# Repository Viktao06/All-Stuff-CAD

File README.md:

Welcome! These are some of my works related to Computer Aided-Design (CAD). While they might not be the most beautiful or most efficient drawings, 
they helped me gain experience using computers to draw schematics, mechanical drawings and eventually, their 3D form.

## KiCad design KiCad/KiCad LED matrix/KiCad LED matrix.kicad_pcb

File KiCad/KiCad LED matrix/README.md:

This design was one of our candidates for printing and building our LED matrix animation project on. 
Although the design was a little bulky and wasn't chosen in the end, it was still fun to make and helped me familiarize myself with KiCAD.

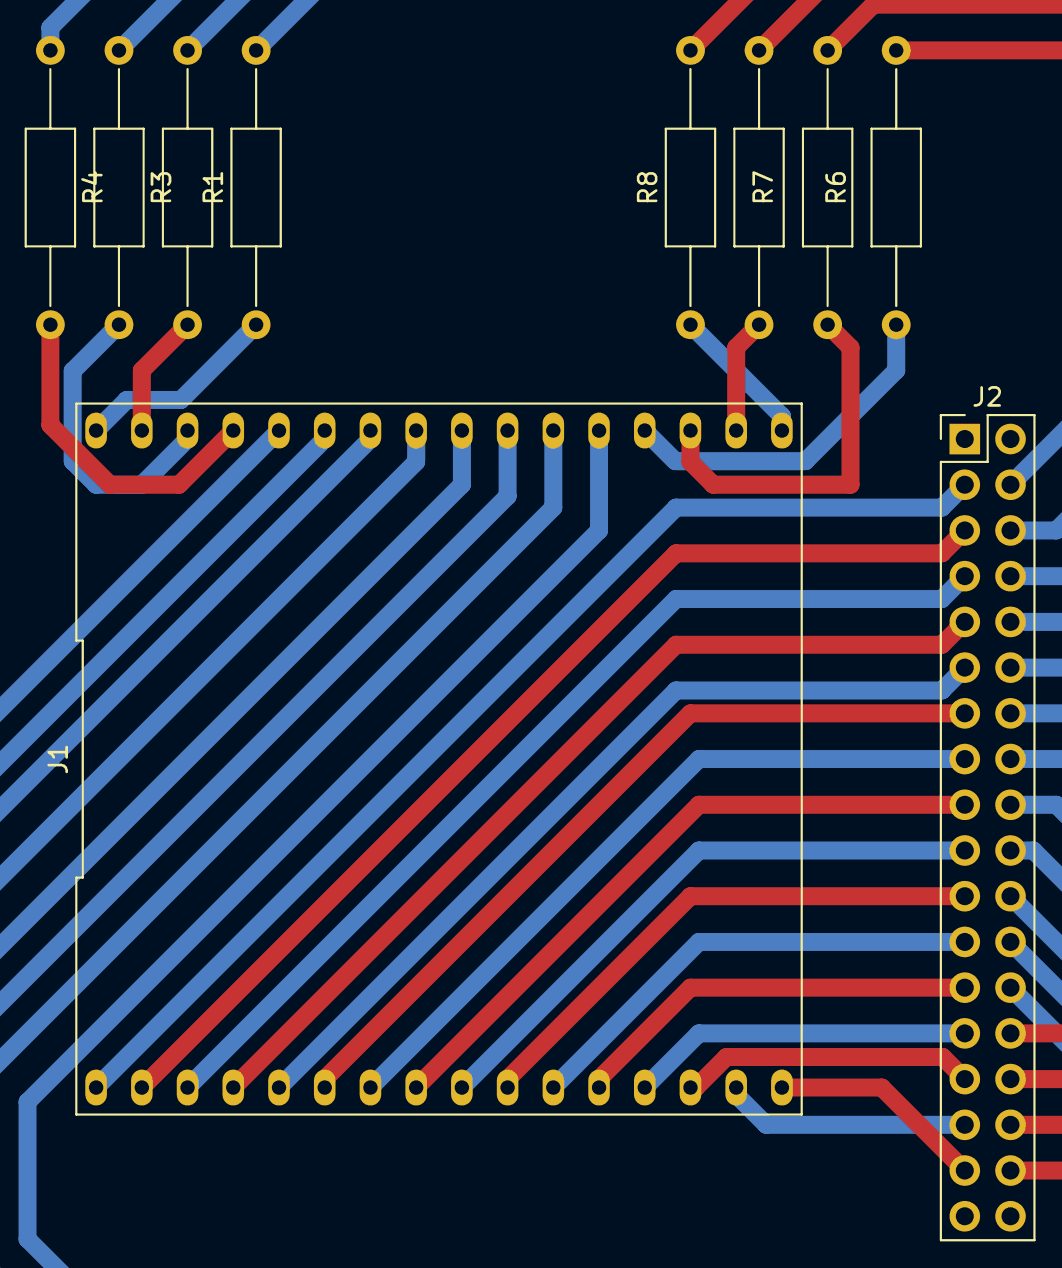
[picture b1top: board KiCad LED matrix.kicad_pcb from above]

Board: 2 copper layers, 10 parts (0 on the bottom side), 40 nets.

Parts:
J1: Matrix Connection; RGB Matrix 2.54 pitch
J2: Conn_02x18_Counter_Clockwise; PinHeader_2x18_P2.54mm_Vertical
R1, R2, R3, R4, R5, R6, R7, R8: 330; R_Axial_DIN0207_L6.3mm_D2.5mm_P15.24mm_Horizontal

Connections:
unnamed: J1.1, J2.1
unnamed: J1.2, J2.2
unnamed: J1.3, J2.3
unnamed: J1.4, J2.4
unnamed: J1.5, J2.5
unnamed: J1.6, J2.6
unnamed: J1.7, J2.7
unnamed: J1.8, J2.8
unnamed: J1.9, J2.9
unnamed: J1.10, J2.10
unnamed: J1.11, J2.11
unnamed: J1.12, J2.12
unnamed: J1.13, J2.13
unnamed: J1.14, J2.14
unnamed: J1.15, J2.15
unnamed: J1.16, J2.16
unnamed: J1.17, R1.1
unnamed: J1.18, R2.2
unnamed: J1.19, R3.2
unnamed: J1.20, R4.2
unnamed: J1.21, J2.21
unnamed: J1.22, J2.22
unnamed: J1.23, J2.23
unnamed: J1.24, J2.24
unnamed: J1.25, J2.25
unnamed: J1.26, J2.26
unnamed: J1.27, J2.27
unnamed: J1.28, J2.28
unnamed: J1.29, R5.1
unnamed: J1.30, R6.1
unnamed: J1.31, R7.1
unnamed: J1.32, R8.1
unnamed: J2.17, R1.2
unnamed: J2.18, R2.1
unnamed: J2.19, R3.1
unnamed: J2.20, R4.1
unnamed: J2.29, R5.2
unnamed: J2.30, R6.2
unnamed: J2.31, R7.2
unnamed: J2.32, R8.2

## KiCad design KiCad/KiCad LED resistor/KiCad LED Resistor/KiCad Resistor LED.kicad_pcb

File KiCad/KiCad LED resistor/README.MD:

My very first experience using KiCAD. We made a simple schematic and drawing of a battery connected to a resistor and an LED. The drawing seemed to come out fine.

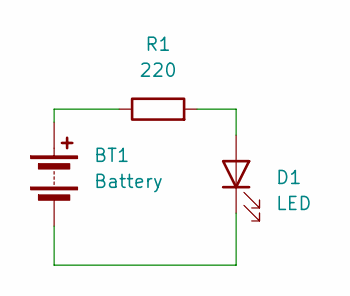
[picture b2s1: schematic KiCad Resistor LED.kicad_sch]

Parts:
BT1: Battery; BatteryHolder_Keystone_1060_1x2032
D1: LED; LED_D8.0mm
R1: 220; R_Axial_DIN0207_L6.3mm_D2.5mm_P10.16mm_Horizontal

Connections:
unnamed: BT1.1 (+), R1.1
unnamed: BT1.2 (-), D1.1 (K)
unnamed: D1.2 (A), R1.2

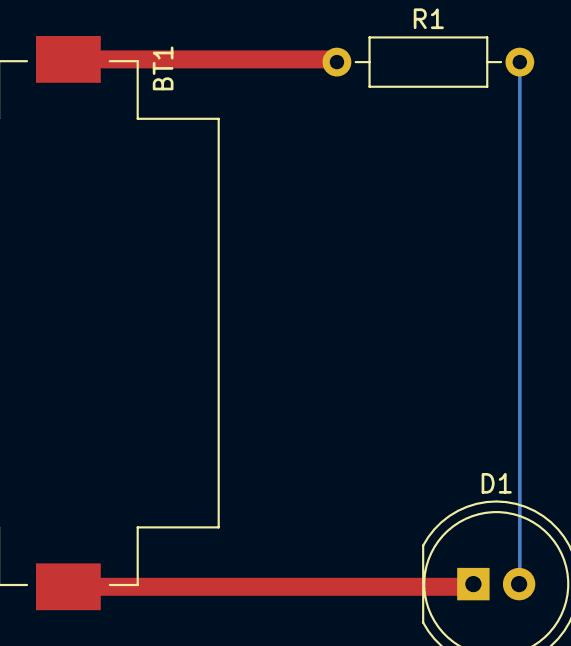
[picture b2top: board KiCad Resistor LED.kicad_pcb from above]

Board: 2 copper layers, 3 parts (0 on the bottom side), 3 nets.

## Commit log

2025-10-16 KiCAD Upload
